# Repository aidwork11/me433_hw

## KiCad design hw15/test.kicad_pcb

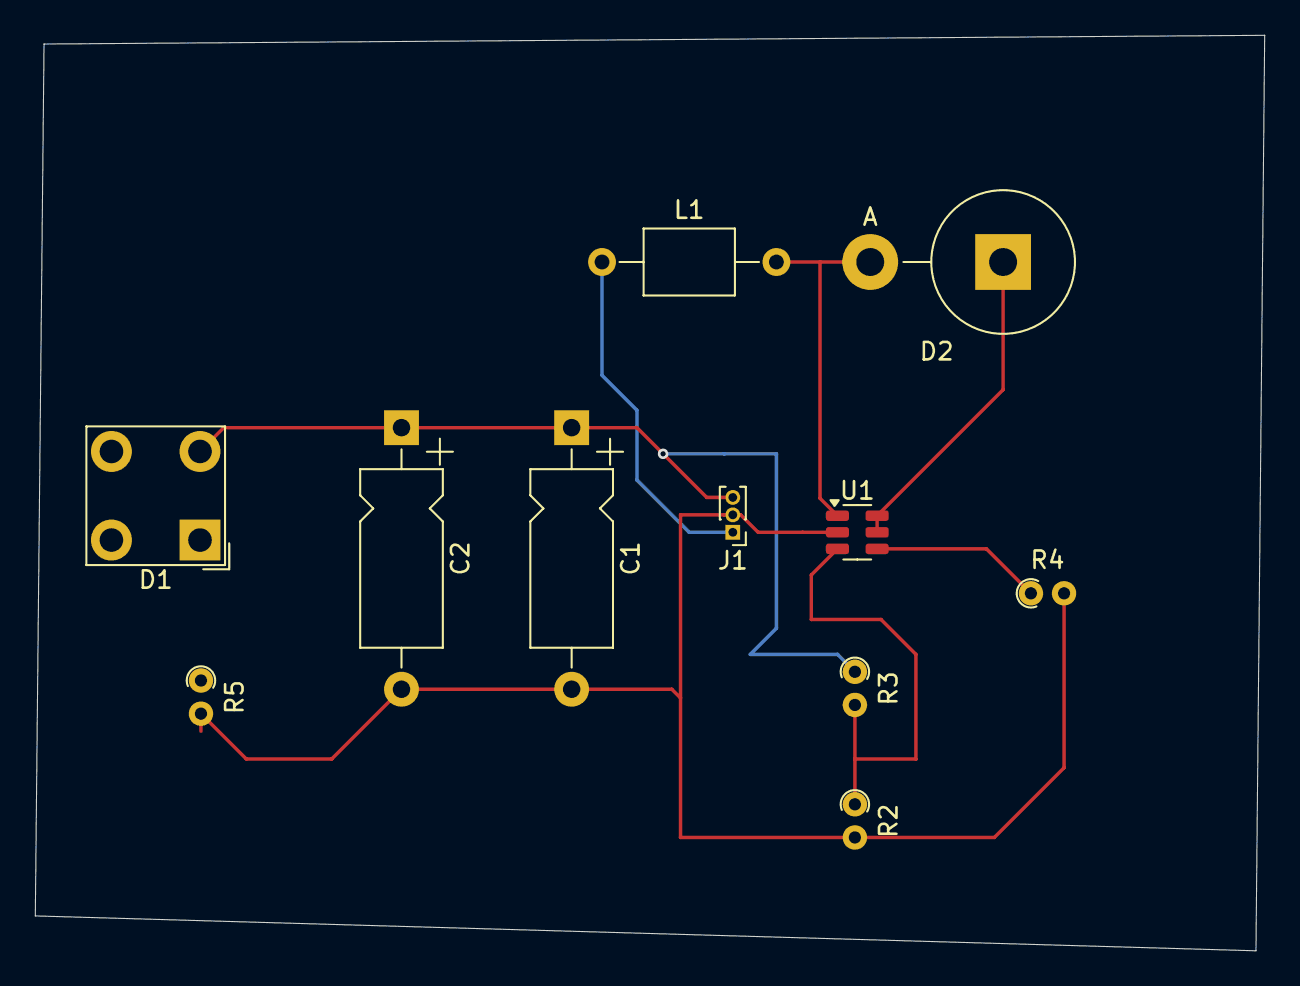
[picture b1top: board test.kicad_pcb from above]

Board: 2 copper layers, 70.5 x 52.5 mm, 11 parts (0 on the bottom side), 7 nets.

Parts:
C1, C2: 22 uF; CP_Axial_L10.0mm_D4.5mm_P15.00mm_Horizontal
D1: LED; LED_BL-FL7680RGB
D2: D_Schottky; D_5KPW_P7.62mm_Vertical_AnodeUp
J1: Conn_01x03_Pin; PinHeader_1x03_P1.00mm_Vertical
L1: 4.7uH; L_Axial_L5.0mm_D3.6mm_P10.00mm_Horizontal_Murata_BL01RN1A2A2
R2, R3: 150 ohm; R_Axial_DIN0204_L3.6mm_D1.6mm_P1.90mm_Vertical
R4: 20k; R_Axial_DIN0204_L3.6mm_D1.6mm_P1.90mm_Vertical
R5: 1k; R_Axial_DIN0204_L3.6mm_D1.6mm_P1.90mm_Vertical
U1: SOT-23-6

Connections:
+5V: C1.1, C2.1, D1.2 (A), D2.1 (K), J1.3, R3.1, U1.5 (VIN), U1.6 (EN)
GND: C1.2, C2.2, J1.2, R2.2, R4.2, R5.2, U1.2 (GND)
unnamed: D1.1 (K), R5.1
unnamed: D2.2 (A), L1.2, U1.1 (SW)
unnamed: R2.1, R3.2, U1.3 (FB)
unnamed: R4.1, U1.4 (OC)
VCC: J1.1, L1.1

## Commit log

2025-05-08 hw11
2025-05-15 hw13
2025-05-22 hw15
2025-05-27 hw16
2025-06-02 hw12 v2
2025-06-02 hw17
